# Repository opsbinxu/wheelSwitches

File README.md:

# wheelSwitches
Bluetooth steering wheel switch

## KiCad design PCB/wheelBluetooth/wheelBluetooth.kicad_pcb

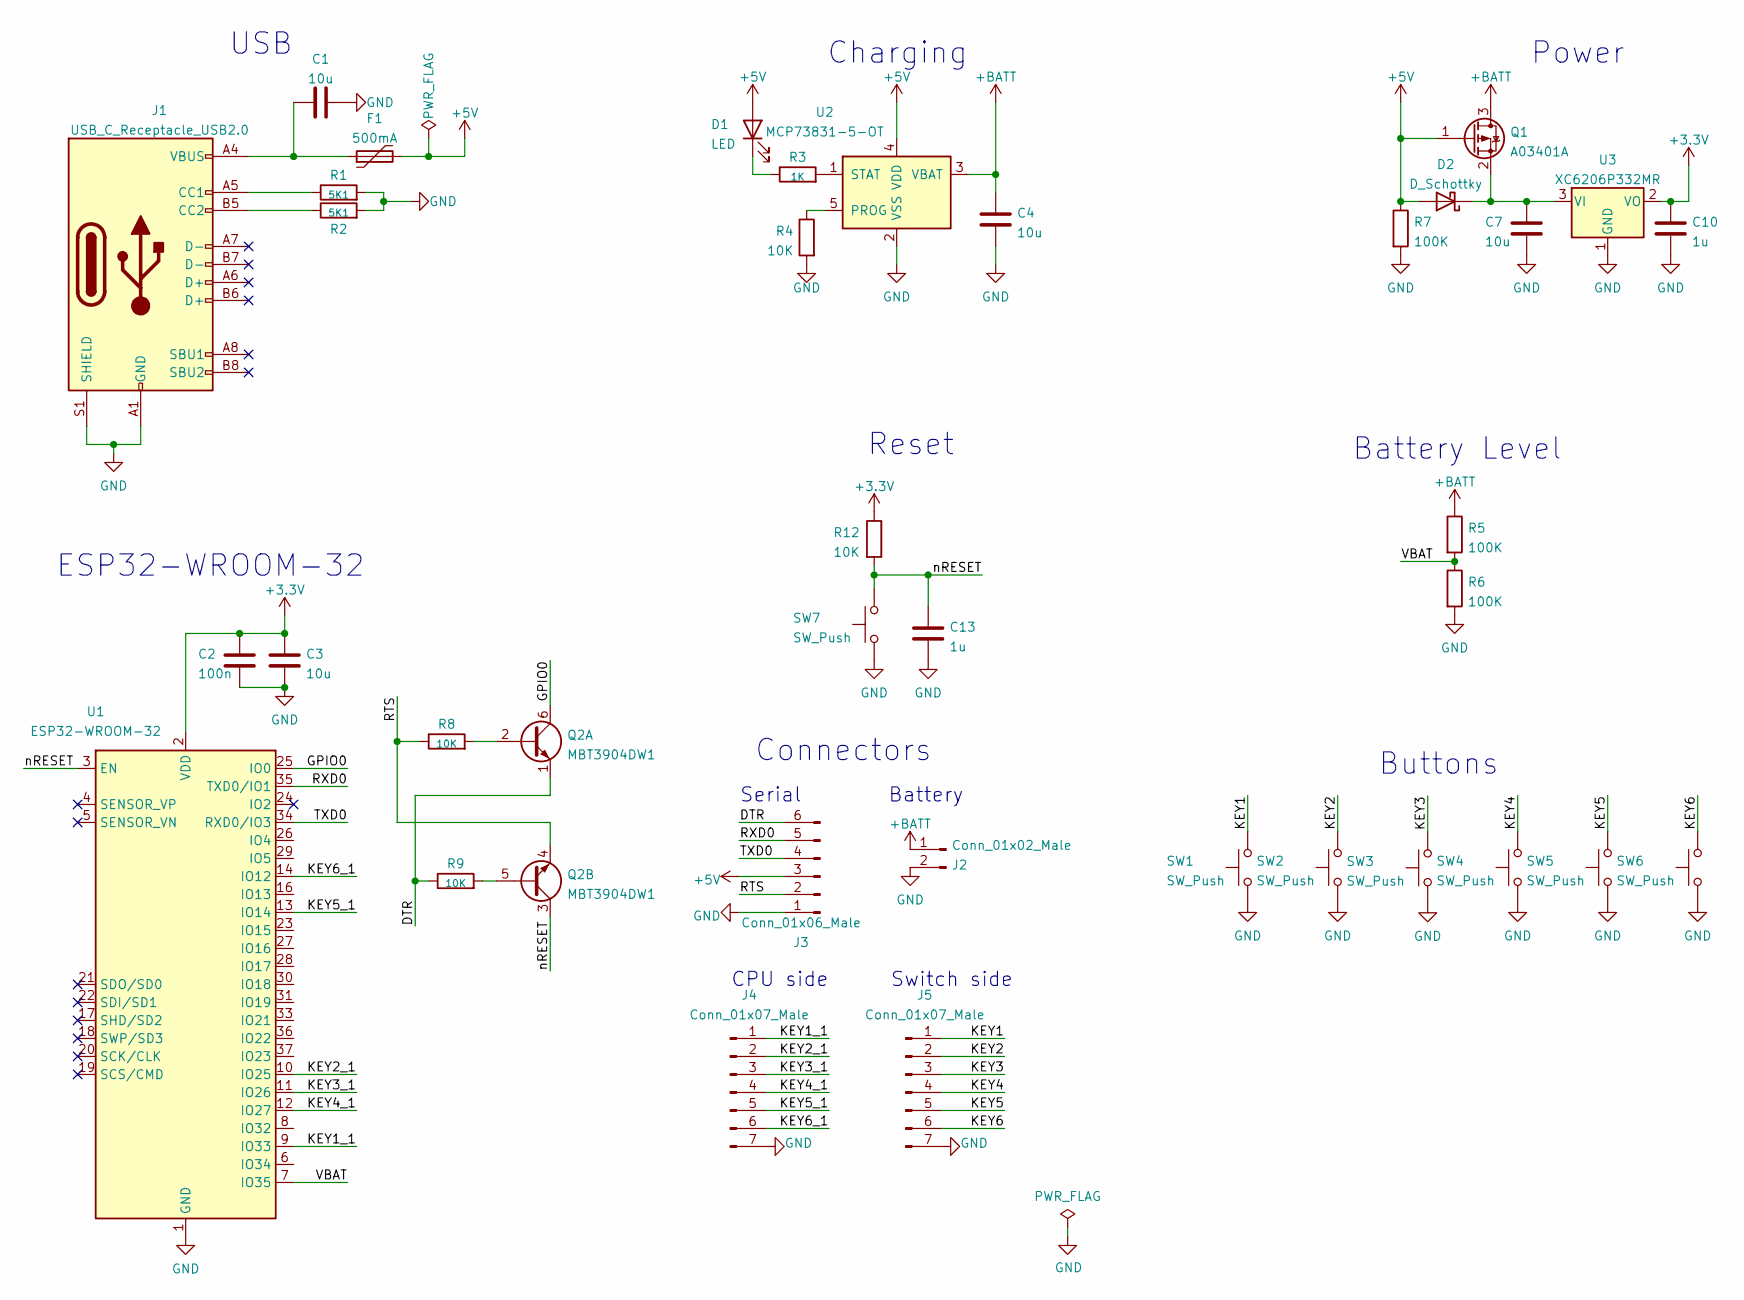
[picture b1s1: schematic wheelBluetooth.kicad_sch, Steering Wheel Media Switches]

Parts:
C1, C3, C4, C7: 10u; C_0603_1608Metric
C2: 100n; C_0603_1608Metric
C10, C13: 1u; C_0603_1608Metric
D1: LED; LED_0603_1608Metric
D2: D_Schottky; D_SOD-123F
F1: 500mA; Fuse_0805_2012Metric
J1: USB_C_Receptacle_USB2.0; USB_C_Receptacle_HRO_TYPE-C-31-M-12
J2: Conn_01x02_Male; JST_PH_S2B-PH-SM4-TB_1x02-1MP_P2.00mm_Horizontal
J3: Conn_01x06_Male; 6_PIN_THT_Staggered
J4, J5: Conn_01x07_Male; PinSocket_1x07_P2.54mm_Vertical
Q1: A03401A; SOT-23
Q2: MBT3904DW1; SOT-363_SC-70-6
R1, R2: 5K1; R_0603_1608Metric
R3: 1K; R_0603_1608Metric
R4, R8, R9, R12: 10K; R_0603_1608Metric
R5, R6, R7: 100K; R_0603_1608Metric
SW1, SW2, SW3, SW4, SW5, SW6: SW_Push; Switch_SMT_SKPMAPE010
SW7: SW_Push; SW_Push_KMR2
U1: ESP32-WROOM-32
U2: MCP73831-5-OT; SOT-23-5
U3: XC6206P332MR; SOT-23

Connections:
+3V3: C2.2, C3.2, C10.1, R12.1, U1.2 (VDD), U3.2 (VO)
+5V: D1.2 (A), D2.2 (A), F1.2, J3.3, Q1.1 (G), R7.1, U2.4 (VDD)
+BATT: C4.2, J2.1, Q1.3 (D), R5.1, U2.3 (VBAT)
/DTR: J3.6, Q2.1 (E1), R9.1
/GPIO0: Q2.6 (C1), U1.25 (IO0)
/KEY1: J5.1, SW1.2
/KEY1_1: J4.1, U1.9 (IO33)
/KEY2: J5.2, SW2.2
/KEY2_1: J4.2, U1.10 (IO25)
/KEY3: J5.3, SW3.2
/KEY3_1: J4.3, U1.11 (IO26)
/KEY4: J5.4, SW4.2
/KEY4_1: J4.4, U1.12 (IO27)
/KEY5: J5.5, SW5.2
/KEY5_1: J4.5, U1.13 (IO14)
/KEY6: J5.6, SW6.2
/KEY6_1: J4.6, U1.14 (IO12)
/RTS: J3.2, Q2.4 (E2), R8.1
/RXD0: J3.5, U1.35 (TXD0/IO1)
/TXD0: J3.4, U1.34 (RXD0/IO3)
/VBAT: R5.2, R6.1, U1.7 (IO35)
/nRESET: C13.1, Q2.3 (C2), R12.2, SW7.2, U1.3 (EN)
GND: C1.2, C2.1, C3.1, C4.1, C7.2, C10.2, C13.2, J1.A1 (GND), J1.A12 (GND), J1.B1 (GND), J1.B12 (GND), J1.S1 (SHIELD), J2.2, J3.1, J4.7, J5.7, R1.2, R2.2, R4.2, R6.2, R7.2, SW1.1, SW2.1, SW3.1, SW4.1, SW5.1, SW6.1, SW7.1, U1.1 (GND), U1.15 (GND), U1.38 (GND), U1.39 (GND), U2.2 (VSS), U3.1 (GND)
unnamed: C1.1, F1.1, J1.A4 (VBUS), J1.A9 (VBUS), J1.B4 (VBUS), J1.B9 (VBUS)
unnamed: C7.1, D2.1 (K), Q1.2 (S), U3.3 (VI)
unnamed: D1.1 (K), R3.1
unnamed: J1.A5 (CC1), R1.1
unnamed: J1.B5 (CC2), R2.1
unnamed: Q2.2 (B1), R8.2
unnamed: Q2.5 (B2), R9.2
unnamed: R3.2, U2.1 (STAT)
unnamed: R4.1, U2.5 (PROG)

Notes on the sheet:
USB
ESP32-WROOM-32
Serial
CPU side
Connectors
Reset
Battery
Charging
Switch side
Buttons
Battery Level
Power

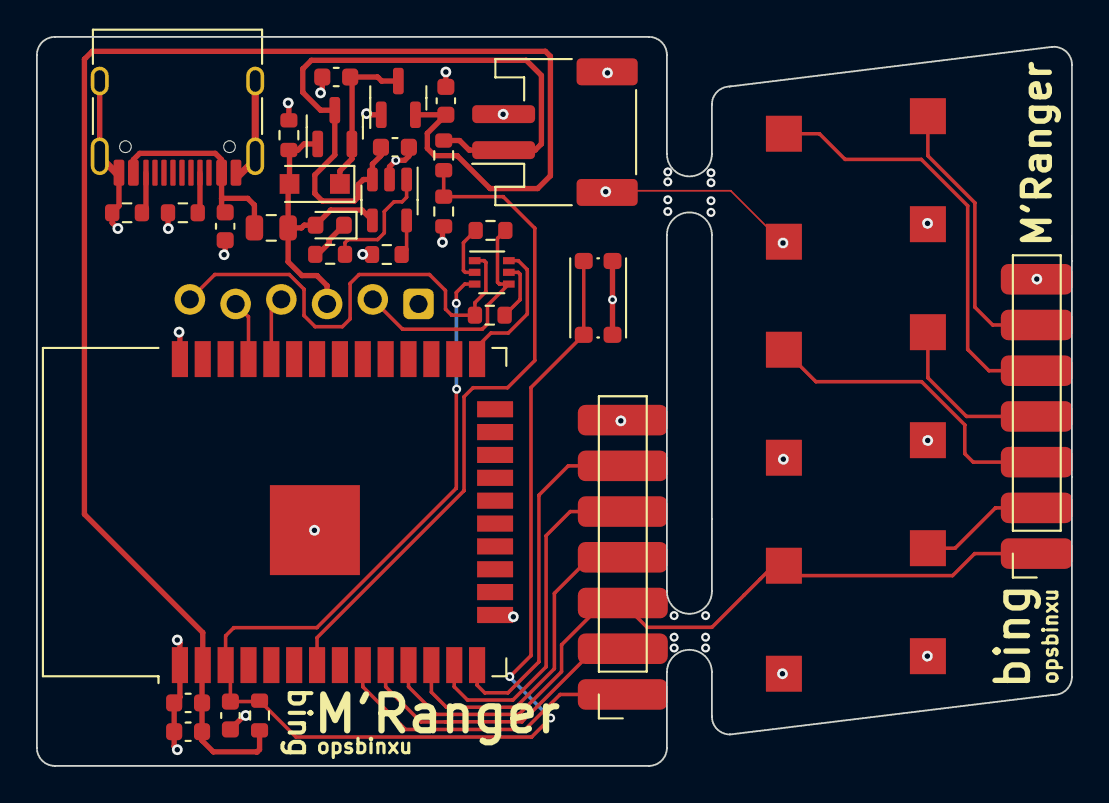
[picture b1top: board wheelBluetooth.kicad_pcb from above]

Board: 2 copper layers, 57.5 x 40.5 mm, 37 parts (0 on the bottom side), 32 nets.

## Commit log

2021-08-18 Create schematic
2021-08-27 Schematic
2021-08-27 Cloned josh's kicad lib
2021-08-27 Schematic update and PCB
2021-08-28 Updated PCB
2021-08-29 PCB graphics
2021-08-30 Update PCB
2021-10-14 Fixed reset circuit
